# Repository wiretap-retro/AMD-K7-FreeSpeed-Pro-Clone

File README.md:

# AMD K7 FreeSpeed Pro Clone
This device attaches to the AMD K7 debug port and provides for overclocking. It is a clone of the FreeSpeed Pro by Ninja Micros.

## Vogons.org Project
URL: https://www.vogons.org/viewtopic.php?t=71328

## Project Status
Tested and working by numerous people. Results may vary based on CPU and motherboard support.

## Building / Installing
This repository contains the KiCAD files, Gerbers, BOM and Pick & Place files. The BOM and Pick & Place files are formatted for JLCPCB assembly. They can be directly uploaded along with the Gerbers for their SMT assembly service. Parts subsitutions may be required if certain components are out of stock due to component/chip shortages. Through-hole components are to be soldered after you receive the board from JLCPCB.
* If performing assembly the assembly entirely by hand, solder all SMD components on the back first, along with the 4-pin molex connector.
* Next, solder the dip switches, socket connector, and LED. That's it!
* Refer to the Ninjamicro Jumper Settings picture in the repository to set your DIP switches properly. Don't start out with too aggressive of an overclock.
* On your AMD K7 CPU, open the casing to expose the debug connector.
* Plug the FreeSpeed device into the connector and attach a 4-pin molex cable.
* Test boot the machine and have fun.

## Optional
You can cut the AMD K7's housing with a pair of side cutters and file to make the FreeSpeed Pro fit while the shroud is installed. Measure twice, cut once. 

## Miscellaneous
This is an open hardware design, so do what you want with it. I tried contacting the original creator through all points of contact I could find, and there was no answer back. There are no copyright, trademark, or registration marks on the original device and the website no longer exists. This device also very closely matches the schematics in the Tom's Hardware article from November 13th, 1999 titled "Make Your Own Athlon Overclocking Device".

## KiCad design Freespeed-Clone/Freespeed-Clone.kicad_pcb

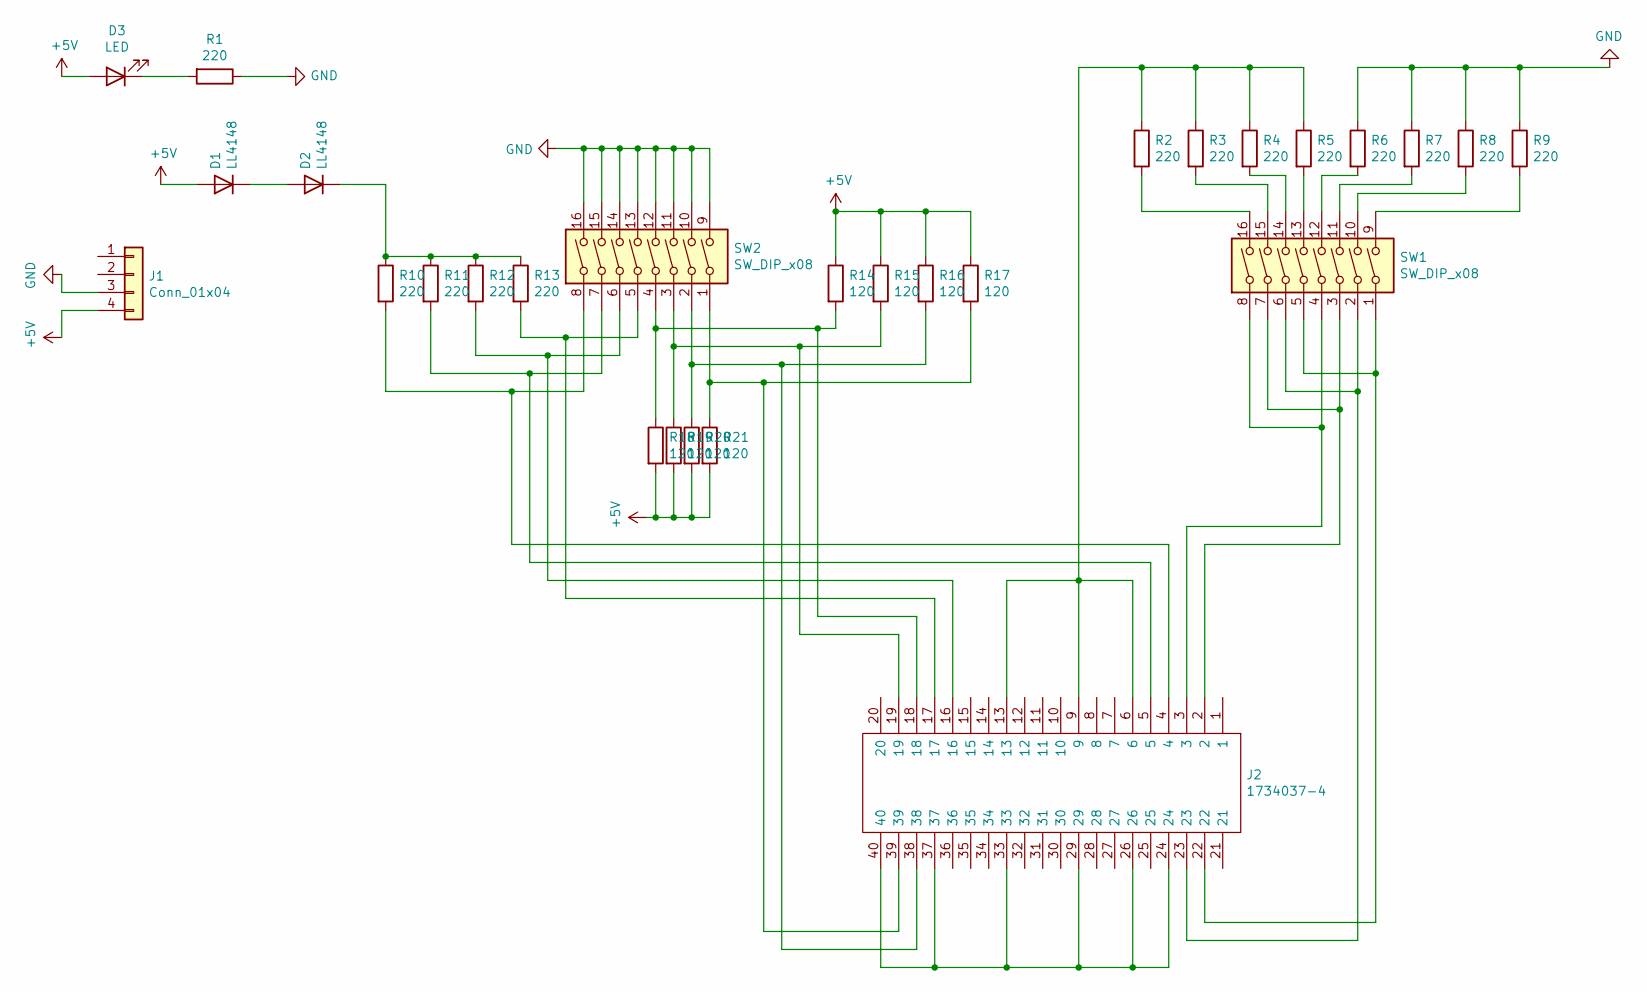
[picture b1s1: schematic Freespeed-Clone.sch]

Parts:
D1, D2: LL4148; D_MiniMELF_Handsoldering
D3: LED; LED_D3.0mm
J1: Conn_01x04; SHDR4W166P0X508_1X4_2326X828X1066P
J2: 1734037-4; 17340374; Mouser Part Number 571-1734037-4
R1, R2, R3, R4, R5, R6, R7, R8, R9, R10, R11, R12, R13: 220; R_1206_3216Metric_Pad1.42x1.75mm_HandSolder
R14, R15, R16, R17, R18, R19, R20, R21: 120; R_1206_3216Metric_Pad1.42x1.75mm_HandSolder
SW1, SW2: SW_DIP_x08; SW_DIP_SPSTx08_Slide_9.78x22.5mm_W7.62mm_P2.54mm

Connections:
+5V: D1.2 (A), D3.2 (A), J1.4, R14.1, R15.1, R16.1, R17.1, R18.2, R19.2, R20.2, R21.2
GND: J1.3, R1.1, R6.1, R7.1, R8.1, R9.1, SW2.9, SW2.10, SW2.11, SW2.12, SW2.13, SW2.14, SW2.15, SW2.16
unnamed: D1.1 (K), D2.2 (A)
unnamed: D2.1 (K), R10.1, R11.1, R12.1, R13.1
unnamed: D3.1 (K), R1.2
unnamed: J2.2, SW1.3, SW1.7
unnamed: J2.3, SW1.4, SW1.8
unnamed: J2.4, R10.2, SW2.8
unnamed: J2.5, R11.2, SW2.7
unnamed: J2.6, J2.9, J2.13, R2.1, R3.1, R4.1, R5.1
unnamed: J2.16, R12.2, SW2.6
unnamed: J2.17, R13.2, SW2.5
unnamed: J2.18, R14.2, R18.1, SW2.4
unnamed: J2.19, R15.2, R19.1, SW2.3
unnamed: J2.22, SW1.1, SW1.5
unnamed: J2.23, SW1.2, SW1.6
unnamed: J2.24, J2.26, J2.29, J2.33, J2.37, J2.40
unnamed: J2.38, R16.2, R20.1, SW2.2
unnamed: J2.39, R17.2, R21.1, SW2.1
unnamed: R2.2, SW1.16
unnamed: R3.2, SW1.15
unnamed: R4.2, SW1.14
unnamed: R5.2, SW1.13
unnamed: R6.2, SW1.12
unnamed: R7.2, SW1.11
unnamed: R8.2, SW1.10
unnamed: R9.2, SW1.9

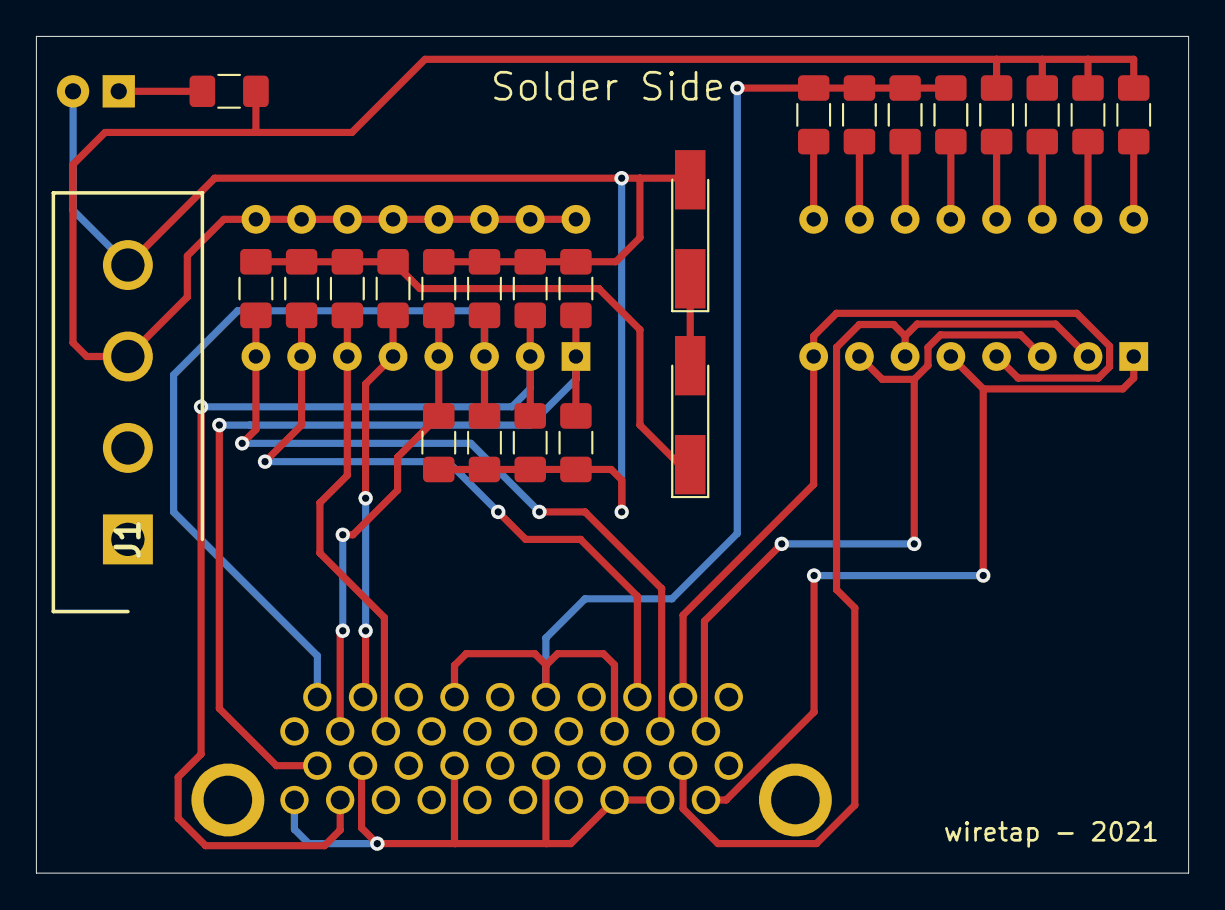
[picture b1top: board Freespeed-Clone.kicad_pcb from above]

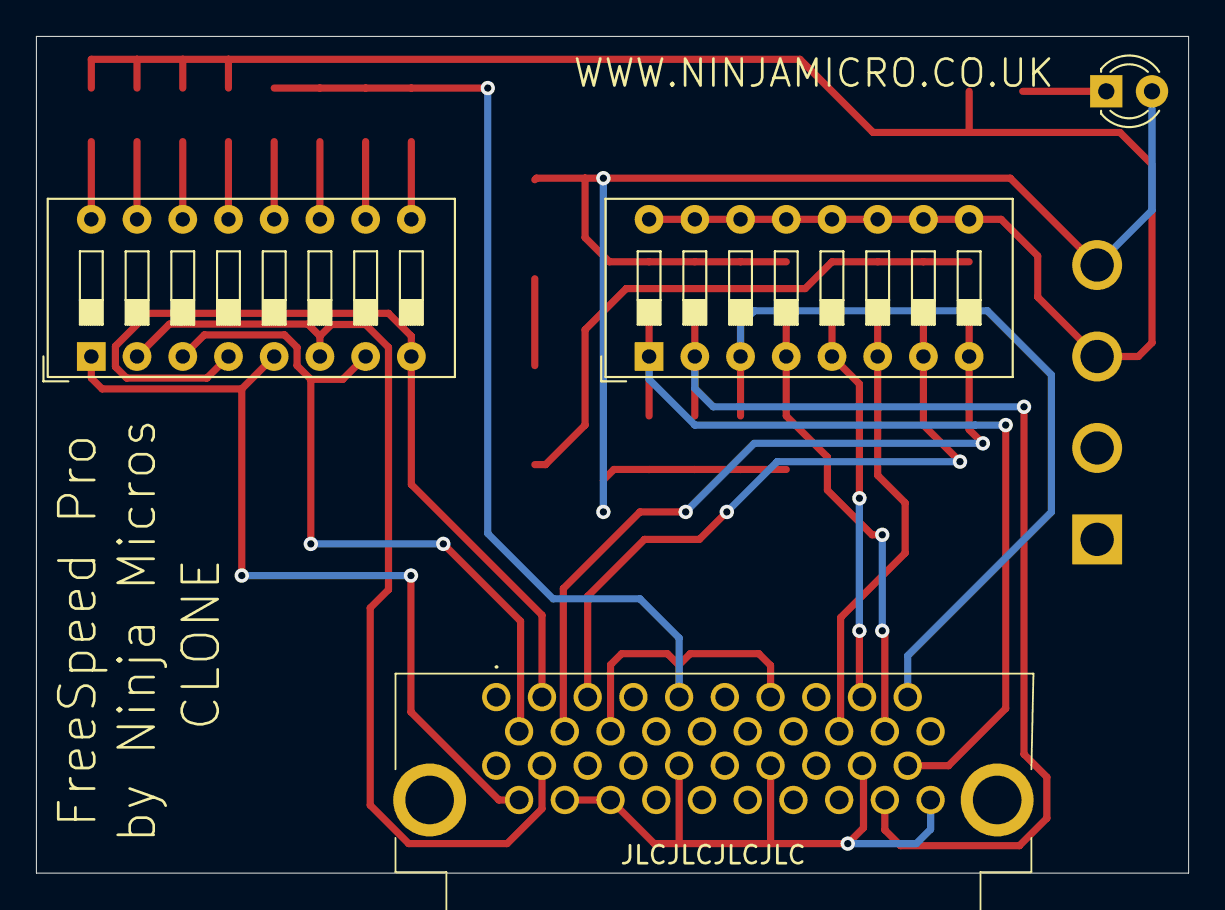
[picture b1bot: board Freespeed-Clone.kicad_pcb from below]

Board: 2 copper layers, 64.0 x 46.5 mm, 28 parts (4 on the bottom side), 27 nets.

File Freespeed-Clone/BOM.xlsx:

Reference | Value | Manufacturer | Part # | Mouser Part # | Footprint
D1, D2 | LL4148 | ON Semiconductor | FDLL4148 | 512-FDLL4148 | SMD: Mini-MELF / LL-34 / SOD-80 / DO213-AA
D3 |  | Lite-On | LTL-4221N | 859-LTL-4221N | THT: LED 3.0mm
J1 |  | TE Connectivity | 350211-1 | 571-3502111 | THT: TE Connectivity 350211-1
J2 |  | TE Connectivity | 1734037-4 | 571-1734037-4 | THT: TE Connectivity 1734037-4
R1, R2, R3, R4, R5, R6, R7, R8, R9, R10, R11, R12, R13 | 220 Ω | KOA Speer | RK73B2BTTDD221J | 660-RK73B2BTTDD221J | SMD: Resistor 1206_3216Metric_Pad1.42x1.75mm_HandSolder
R14, R15, R16, R17, R18, R19, R20, R21 | 120 Ω | KOA Speer | RK73B2BTTDD121J | 660-RK73B2BTTDD121J | SMD: Resistor 1206_3216Metric_Pad1.42x1.75mm_HandSolder
SW1, SW2 |  | CTS Electronic Components | 206-8ST | 774-2068ST | THT: SW_DIP_SPSTx08_Slide_9.78x22.5mm_W7.62mm_P2.54mm

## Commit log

2022-09-09 Initial upload
